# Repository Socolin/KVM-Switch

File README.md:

# KVM Switch

A KVM Switch for any HID device built with multiple [Raspberry Pi Pico 2](https://www.raspberrypi.com/products/raspberry-pi-pico-2/)

## Status

This project is still in development. The code is almost done, and I need to design the PCB.

So far I can use it as a KVM switch. I can select the computer to use with a keyboard shortcut. I was not able to
test with exotic keyboard / mouse yet, but those should be supported.

The detailed documentation is available at [doc/technical.md](doc/technical.md).

The remaining tasks are: 
- Test with 2 nodes (switch between 3 computers).
- Design PCB for 1 node (and maybe for 2 nodes later)
- Test with 3 hid devices.
- Test `TUD_OPT_HIGH_SPEED`

## Build

### Prerequisites

- cmake
- Clone https://github.com/raspberrypi/pico-sdk
- Clone https://github.com/raspberrypi/picotool

### Build

```sh
git clone git@github.com:Socolin/KVM-Switch.git
cd KVM-Switch
git submodule update --init --recursive
mkdir build
cd build
cmake .. -DPICO_BOARD=pico2 -DPICO_SDK_PATH={PATH_TO_PICOSDK} -DPICOTOOL_FETCH_FROM_GIT_PATH={PATH_TO_PICOTOOL}
make -j
# Then output is in src/node and src/controller
```

### Flash

To simplify flashing both, you can use the serial number of your pico with `picotool info -a` the serial will look like `46AA0E6255B66826`

```sh
picotool load --ser $PICO_PI_NODE_SERIAL -f -x src/node/kvm_node.uf2;
picotool load --ser $PICO_PI_CONTROLLER_SERIAL -f -x src/controller/kvm_controller.uf2;
```

## Hardware Architecture

### 2 Nodes With 2 HIDs

[See Schematic](doc/2_nodes_2_hid/2_nodes_2_hid.pdf)

### 2 Nodes With 3 HIDs

[See Schematic](doc/2_nodes_3_hid/2_nodes_3_hid.pdf)

### 3 Nodes With 3 HIDs

[See Schematic](doc/3_nodes_3_hid/3_nodes_3_hid.pdf)

## Software Architecture

## Configuration UI

The KVM Switch can be configured through a web UI. It can be accessed with a web browser supporting WebUSB.
You can access it at https://socolin.github.io/KVM-Switch/ (You need to use a browser supporting WebUSB)
The code of the config UI is in `tools/configurator`

### Build

If you need to build the tool, you need [Node.js 24](https://nodejs.org/) then run those commands

```
cd tools/configurator
npm install
npm run start
```

Then access it at http://localhost:4200 (You need to use a browser supporting WebUSB)

## AI Usage

Basically, I see AI as a tool, and I have fun writing code, so:

- All the code in `src/` is written by a human.
- AI was used as a learning assistant, to help understand and learn all the USB / HID / Electronic stuff.
- AI was used to review the code.
- AI was used to generate some test cases (but the test logic is human-made) (see `AI-generated` comments).

## History

This project started to fix an issue I had with my current commercial KVM switch, that is the delay to switch between
2 computers; I wanted a shortcut to switch instantaneously. This project is also an opportunity for me to learn a some
few things with electronic and discover dev on a microcontroller. Feel free to provide any feedback, as I'm still
learning.

I first tried to use CH9329 and CH9350 to avoid all the USB parts and get this done quickly. However, during
my testing I discovered that the CH9329 has a HID descriptor that does not expose all the features I wanted (like the
mouse pan) and the CH9350 felt the same way. So I learnt a lot about HID descriptors, tinyUSB, etc… And, now this project
should support any HID device (not just keyboard and mouse) like Gamepad etc… I kept the code I used to use those chips
in `src/legacy` if anyone need this, feel free to use it

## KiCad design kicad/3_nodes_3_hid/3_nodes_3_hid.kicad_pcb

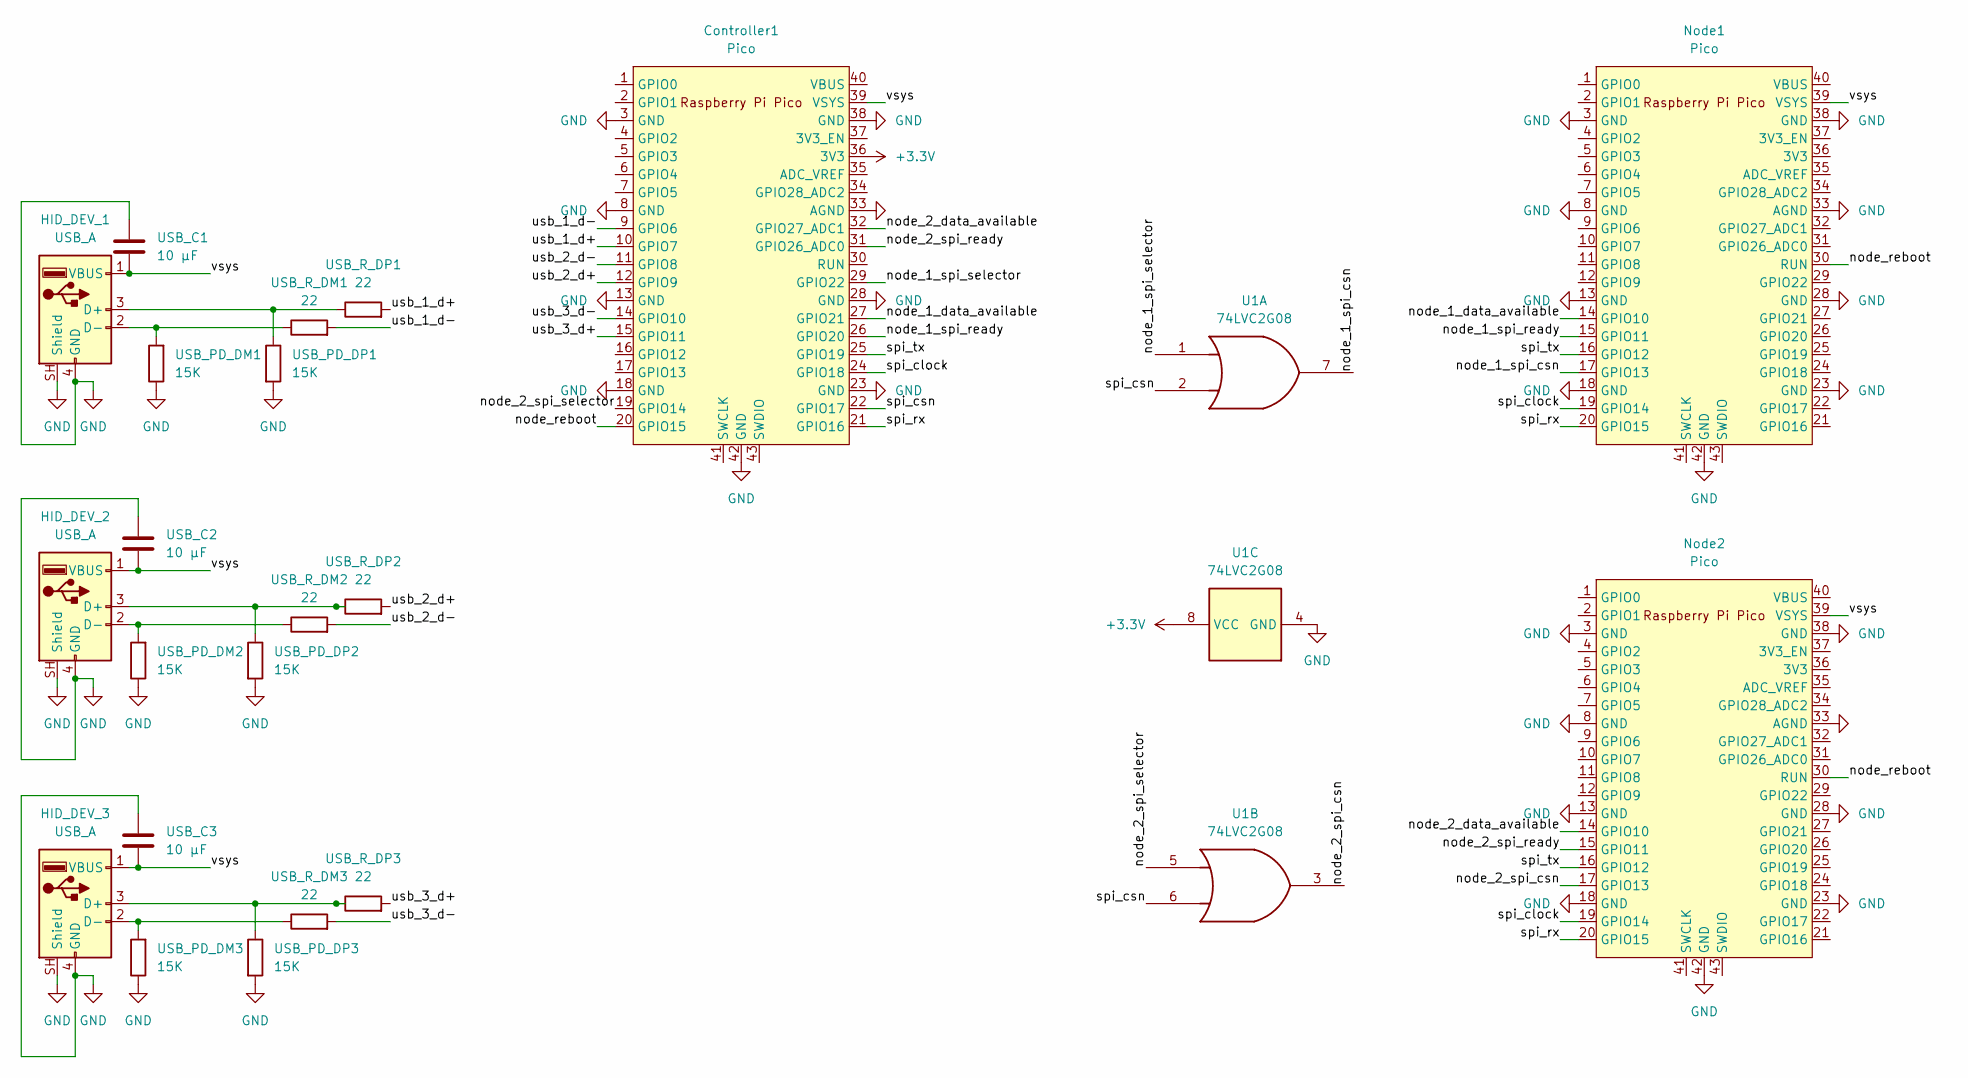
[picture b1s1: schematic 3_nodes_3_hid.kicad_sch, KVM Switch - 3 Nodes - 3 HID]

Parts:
Controller1: Pico; RPi_Pico_SMD_TH
HID_DEV_1, HID_DEV_2, HID_DEV_3: USB_A; USB_A_Molex_67643_Horizontal
Node1, Node2: Pico; RPi_Pico_SMD_TH
U1: 74LVC2G08; TSSOP-8_4.4x3mm_P0.65mm
USB_C1, USB_C2, USB_C3: 10 µF; C_1206_3216Metric_Pad1.33x1.80mm_HandSolder
USB_PD_DM1, USB_PD_DM2, USB_PD_DM3: 15K; R_1206_3216Metric_Pad1.30x1.75mm_HandSolder
USB_PD_DP1, USB_PD_DP2, USB_PD_DP3: 15K; R_1206_3216Metric_Pad1.30x1.75mm_HandSolder
USB_R_DM1, USB_R_DM2, USB_R_DM3: 22; R_1206_3216Metric_Pad1.30x1.75mm_HandSolder
USB_R_DP1, USB_R_DP2, USB_R_DP3: 22; R_1206_3216Metric_Pad1.30x1.75mm_HandSolder

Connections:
+3.3V: Controller1.36 (3V3), U1.8 (VCC)
/node_1_data_available: Controller1.27 (GPIO21), Node1.14 (GPIO10)
/node_1_spi_csn: Node1.17 (GPIO13), U1.7
/node_1_spi_ready: Controller1.26 (GPIO20), Node1.15 (GPIO11)
/node_1_spi_selector: Controller1.29 (GPIO22), U1.1
/node_2_data_available: Controller1.32 (GPIO27_ADC1), Node2.14 (GPIO10)
/node_2_spi_csn: Node2.17 (GPIO13), U1.3
/node_2_spi_ready: Controller1.31 (GPIO26_ADC0), Node2.15 (GPIO11)
/node_2_spi_selector: Controller1.19 (GPIO14), U1.5
/node_reboot: Controller1.20 (GPIO15), Node1.30 (RUN), Node2.30 (RUN)
/spi_clock: Controller1.24 (GPIO18), Node1.19 (GPIO14), Node2.19 (GPIO14)
/spi_csn: Controller1.22 (GPIO17), U1.2, U1.6
/spi_rx: Controller1.21 (GPIO16), Node1.20 (GPIO15), Node2.20 (GPIO15)
/spi_tx: Controller1.25 (GPIO19), Node1.16 (GPIO12), Node2.16 (GPIO12)
/usb_1_d+: Controller1.10 (GPIO7), USB_R_DP1.2
/usb_1_d-: Controller1.9 (GPIO6), USB_R_DM1.2
/usb_2_d+: Controller1.12 (GPIO9), USB_R_DP2.2
/usb_2_d-: Controller1.11 (GPIO8), USB_R_DM2.2
/usb_3_d+: Controller1.15 (GPIO11), USB_R_DP3.2
/usb_3_d-: Controller1.14 (GPIO10), USB_R_DM3.2
/vsys: Controller1.39 (VSYS), HID_DEV_1.1 (VBUS), HID_DEV_2.1 (VBUS), HID_DEV_3.1 (VBUS), Node1.39 (VSYS), Node2.39 (VSYS), USB_C1.2, USB_C2.2, USB_C3.2
GND: Controller1.3 (GND), Controller1.8 (GND), Controller1.13 (GND), Controller1.18 (GND), Controller1.23 (GND), Controller1.28 (GND), Controller1.33 (AGND), Controller1.38 (GND), Controller1.42 (GND), HID_DEV_1.4 (GND), HID_DEV_1.SH (Shield), HID_DEV_2.4 (GND), HID_DEV_2.SH (Shield), HID_DEV_3.4 (GND), HID_DEV_3.SH (Shield), Node1.3 (GND), Node1.8 (GND), Node1.13 (GND), Node1.18 (GND), Node1.23 (GND), Node1.28 (GND), Node1.33 (AGND), Node1.38 (GND), Node1.42 (GND), Node2.3 (GND), Node2.8 (GND), Node2.13 (GND), Node2.18 (GND), Node2.23 (GND), Node2.28 (GND), Node2.33 (AGND), Node2.38 (GND), Node2.42 (GND), U1.4 (GND), USB_C1.1, USB_C2.1, USB_C3.1, USB_PD_DM1.1, USB_PD_DM2.1, USB_PD_DM3.1, USB_PD_DP1.2, USB_PD_DP2.2, USB_PD_DP3.2
unnamed: HID_DEV_1.3 (D+), USB_PD_DP1.1, USB_R_DP1.1
unnamed: HID_DEV_1.2 (D-), USB_PD_DM1.2, USB_R_DM1.1
unnamed: HID_DEV_2.3 (D+), USB_PD_DP2.1, USB_R_DP2.1
unnamed: HID_DEV_2.2 (D-), USB_PD_DM2.2, USB_R_DM2.1
unnamed: HID_DEV_3.3 (D+), USB_PD_DP3.1, USB_R_DP3.1
unnamed: HID_DEV_3.2 (D-), USB_PD_DM3.2, USB_R_DM3.1

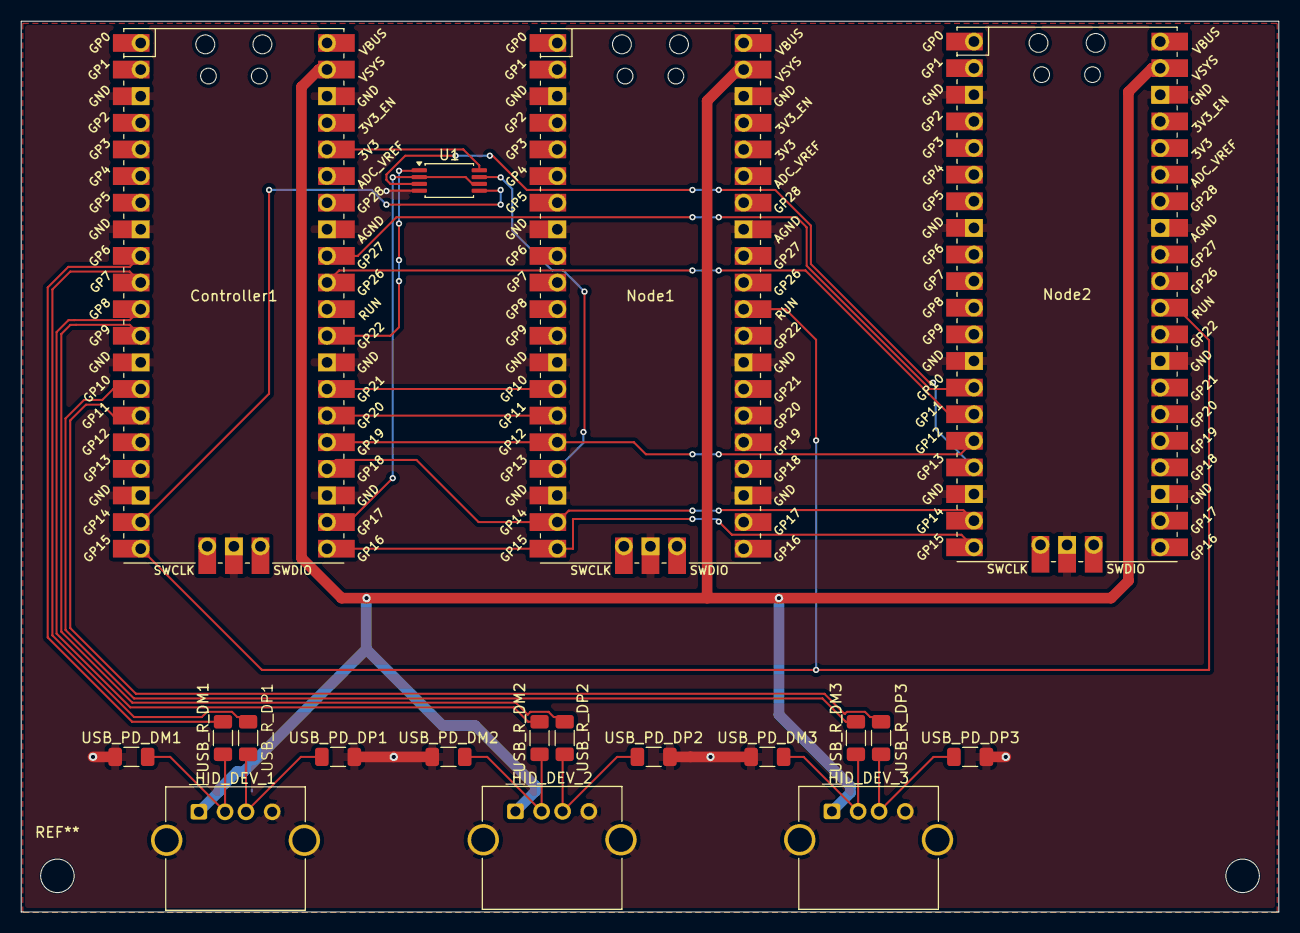
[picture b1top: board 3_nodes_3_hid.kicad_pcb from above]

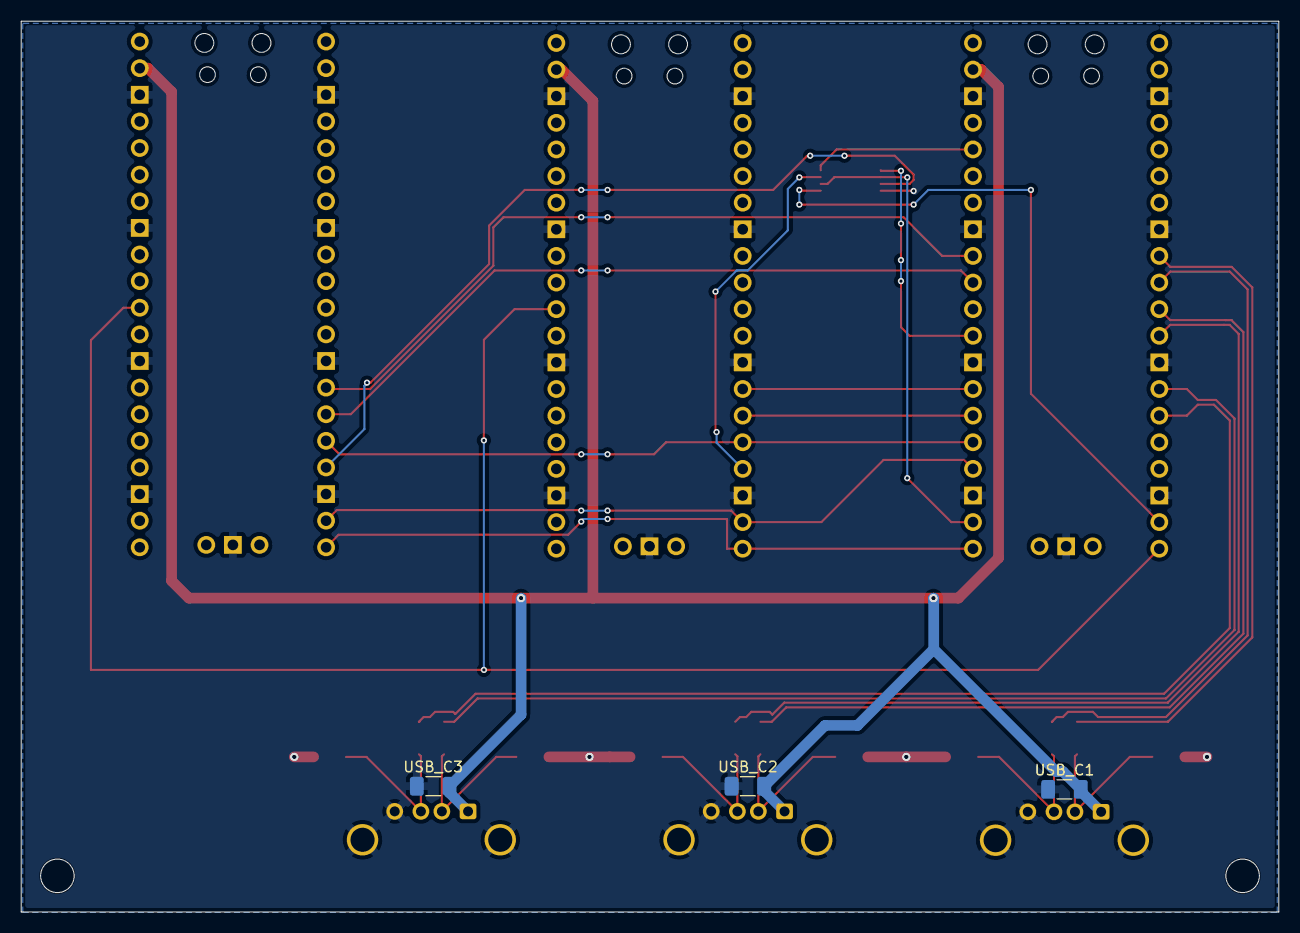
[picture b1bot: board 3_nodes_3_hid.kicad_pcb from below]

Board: 2 copper layers, 120.0 x 85.0 mm, 22 parts (3 on the bottom side), 28 nets.
